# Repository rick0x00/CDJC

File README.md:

# Cascading 4017 Decada/Johnson Counter

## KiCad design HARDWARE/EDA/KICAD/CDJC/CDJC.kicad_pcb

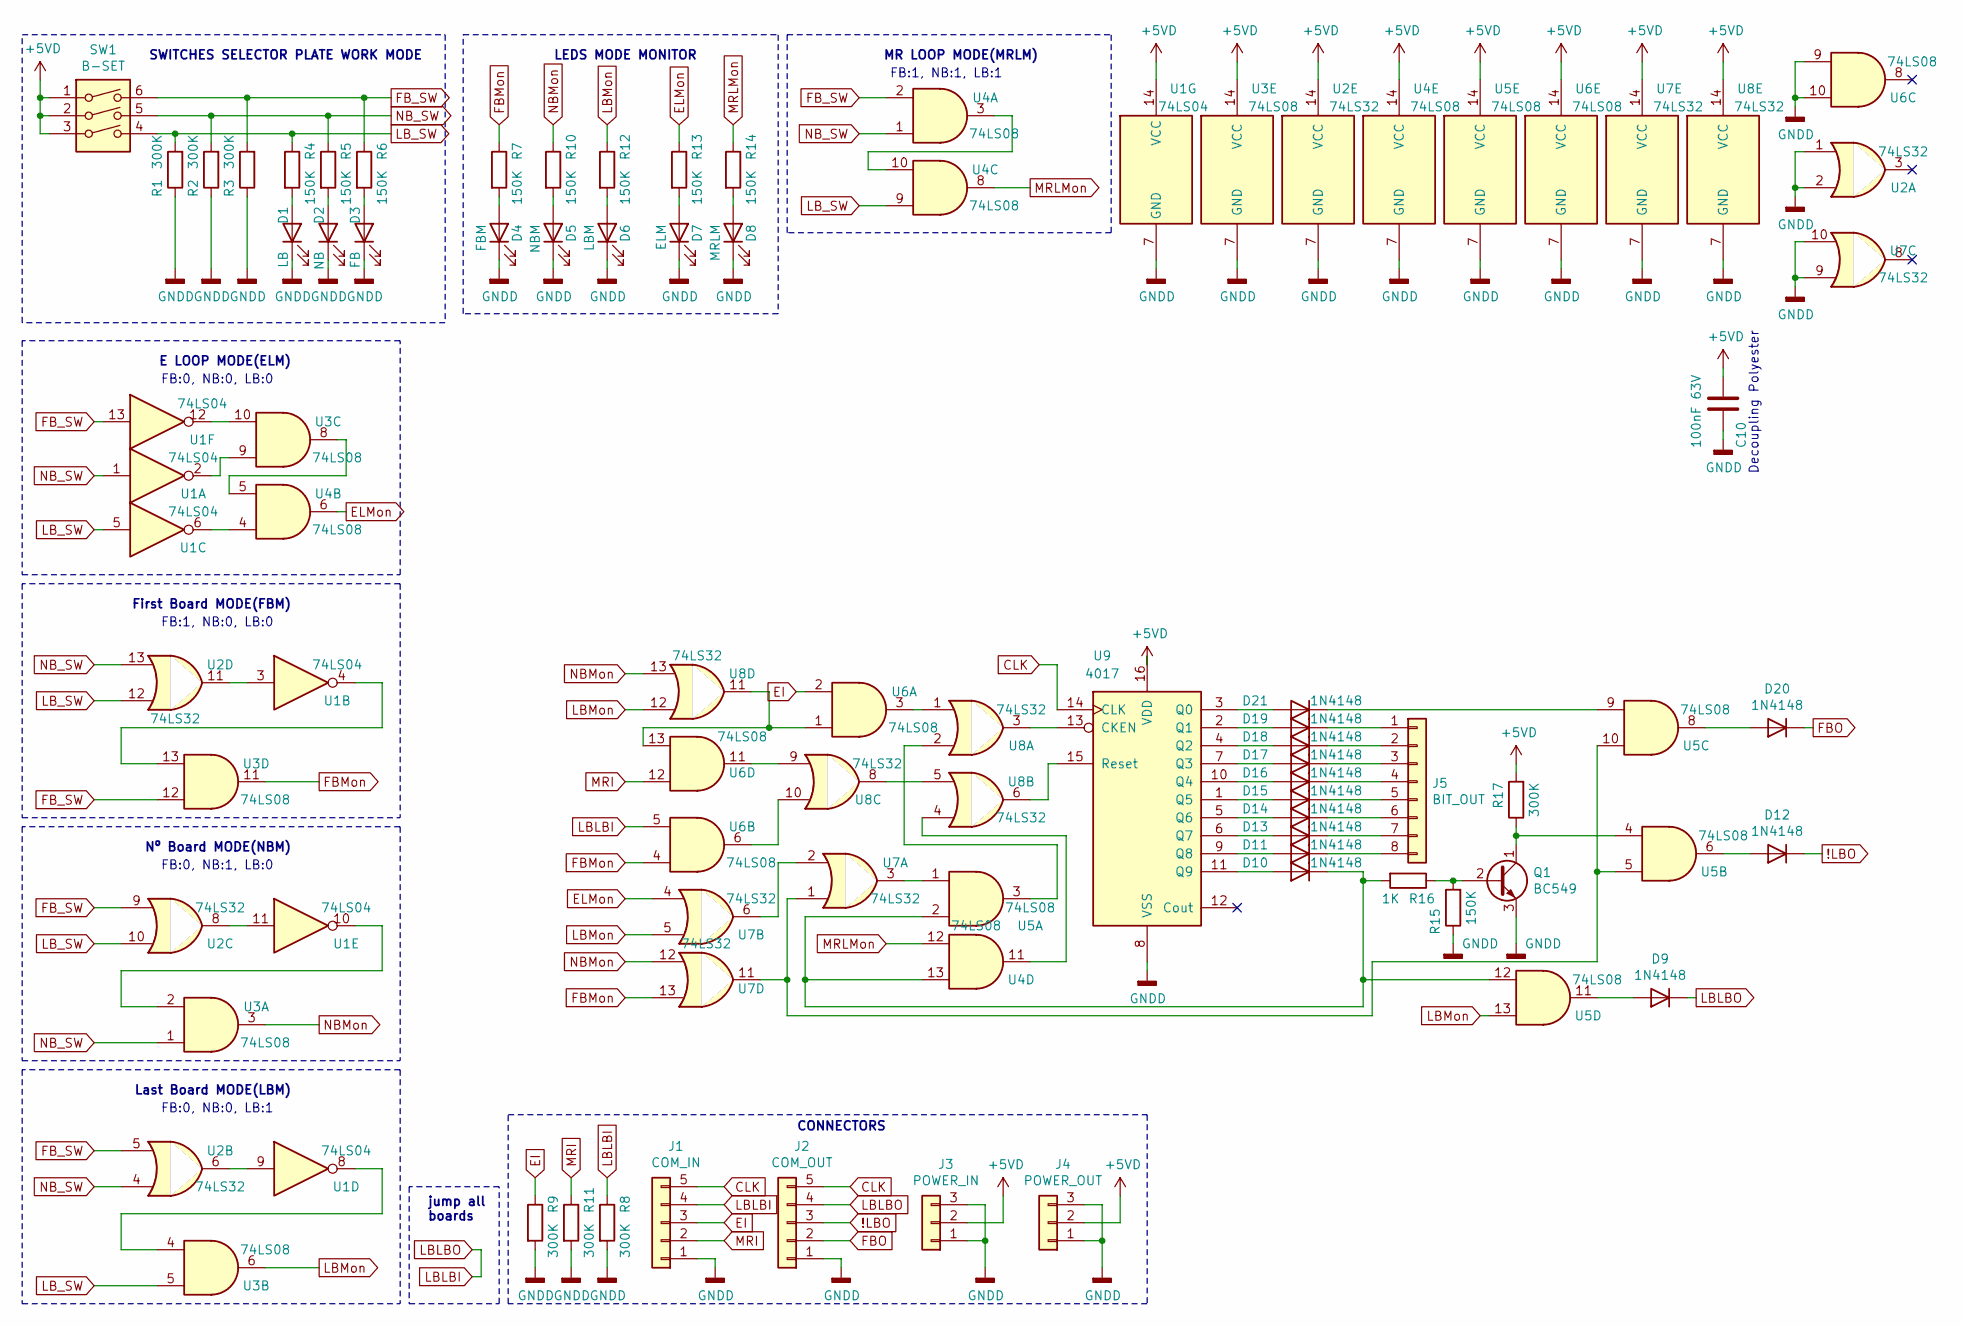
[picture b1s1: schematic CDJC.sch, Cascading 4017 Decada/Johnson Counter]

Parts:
C10: 100nF 63V; C_Rect_L7.0mm_W2.5mm_P5.00mm
D1: LB; LED_D3.0mm
D2: NB; LED_D3.0mm
D3: FB; LED_D3.0mm
D4: FBM; LED_D3.0mm
D5: NBM; LED_D3.0mm
D6: LBM; LED_D3.0mm
D7: ELM; LED_D3.0mm
D8: MRLM; LED_D3.0mm
D9, D10, D11, D12, D13, D14, D15, D16, D17, D18, D19, D20: 1N4148; D_DO-34_SOD68_P7.62mm_Horizontal
D21: 1N4148; D_DO-34_SOD68_P12.70mm_Horizontal
J1: COM_IN; PinHeader_1x05_P2.54mm_Horizontal
J2: COM_OUT; PinSocket_1x05_P2.54mm_Horizontal
J3: POWER_IN; PinHeader_1x03_P2.54mm_Horizontal
J4: POWER_OUT; PinSocket_1x03_P2.54mm_Horizontal
J5: BIT_OUT; PinSocket_1x08_P2.54mm_Horizontal
Q1: BC549; TO-92_Inline
R1, R2, R3, R8, R9, R11, R17: 300K; R_Axial_DIN0207_L6.3mm_D2.5mm_P7.62mm_Horizontal
R4, R5, R6, R7, R10, R12, R13, R14, R15: 150K; R_Axial_DIN0207_L6.3mm_D2.5mm_P7.62mm_Horizontal
R16: 1K; R_Axial_DIN0207_L6.3mm_D2.5mm_P7.62mm_Horizontal
SW1: B-SET; SW_DIP_SPSTx03_Slide_9.78x9.8mm_W7.62mm_P2.54mm
U1: 74LS04; DIP-14_W7.62mm_LongPads
U2, U7, U8: 74LS32; DIP-14_W7.62mm_LongPads
U3, U4, U5, U6: 74LS08; DIP-14_W7.62mm_LongPads
U9: 4017; DIP-16_W7.62mm_LongPads

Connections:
!LBO: D12.1 (K), J2.3
+5VD: C10.1, J3.2, J4.2, R17.2, SW1.1, SW1.2, SW1.3, U1.14 (VCC), U2.14 (VCC), U3.14 (VCC), U4.14 (VCC), U5.14 (VCC), U6.14 (VCC), U7.14 (VCC), U8.14 (VCC), U9.16 (VDD)
CLK: J1.5, J2.5, U9.14 (CLK)
EI: J1.3, R9.1, U6.2
ELMon: R13.1, U4.6, U7.4
FBMon: R7.1, U3.11, U6.4, U7.13
FBO: D20.1 (K), J2.2
FB_SW: R3.2, R6.1, SW1.6, U1.13, U2.5, U2.9, U3.12, U4.2
GNDD: C10.2, D1.1 (K), D2.1 (K), D3.1 (K), D4.1 (K), D5.1 (K), D6.1 (K), D7.1 (K), D8.1 (K), J1.1, J2.1, J3.1, J3.3, J4.1, J4.3, Q1.3 (E), R1.1, R2.1, R3.1, R8.2, R9.2, R11.2, R15.1, U1.7 (GND), U2.1, U2.2, U2.7 (GND), U3.7 (GND), U4.7 (GND), U5.7 (GND), U6.7 (GND), U6.9, U6.10, U7.7 (GND), U7.9, U7.10, U8.7 (GND), U9.8 (VSS)
LBLBI: D9.1 (K), J1.4, J2.4, R8.1, U6.5
LBMon: R12.1, U3.6, U5.13, U7.5, U8.12
LB_SW: R1.2, R4.1, SW1.4, U1.5, U2.10, U2.12, U3.5, U4.9
MRI: J1.2, R11.1, U6.12
MRLMon: R14.1, U4.8, U4.12
NBMon: R10.1, U3.3, U7.12, U8.13
NB_SW: R2.2, R5.1, SW1.5, U1.1, U2.4, U2.13, U3.1, U4.1
unnamed: D1.2 (A), R4.2
unnamed: D2.2 (A), R5.2
unnamed: D3.2 (A), R6.2
unnamed: D4.2 (A), R7.2
unnamed: D5.2 (A), R10.2
unnamed: D6.2 (A), R12.2
unnamed: D7.2 (A), R13.2
unnamed: D8.2 (A), R14.2
unnamed: D9.2 (A), U5.11
unnamed: D10.1 (K), R16.2, U4.13, U5.2, U5.12
unnamed: D10.2 (A), U9.11 (Q9)
unnamed: D11.1 (K), J5.8
unnamed: D11.2 (A), U9.9 (Q8)
unnamed: D12.2 (A), U5.6
unnamed: D13.1 (K), J5.7
unnamed: D13.2 (A), U9.6 (Q7)
unnamed: D14.1 (K), J5.6
unnamed: D14.2 (A), U9.5 (Q6)
unnamed: D15.1 (K), J5.5
unnamed: D15.2 (A), U9.1 (Q5)
unnamed: D16.1 (K), J5.4
unnamed: D16.2 (A), U9.10 (Q4)
unnamed: D17.1 (K), J5.3
unnamed: D17.2 (A), U9.7 (Q3)
unnamed: D18.1 (K), J5.2
unnamed: D18.2 (A), U9.4 (Q2)
unnamed: D19.1 (K), J5.1
unnamed: D19.2 (A), U9.2 (Q1)
unnamed: D20.2 (A), U5.8
unnamed: D21.1 (K), U5.9
unnamed: D21.2 (A), U9.3 (Q0)
unnamed: Q1.1 (C), R17.1, U5.4
unnamed: Q1.2 (B), R15.2, R16.1
unnamed: U1.2, U3.9
unnamed: U1.3, U2.11
unnamed: U1.4, U3.13
unnamed: U1.6, U4.4
unnamed: U1.8, U3.4
unnamed: U1.9, U2.6
unnamed: U1.10, U3.2
unnamed: U1.11, U2.8
unnamed: U1.12, U3.10
unnamed: U3.8, U4.5
unnamed: U4.3, U4.10
unnamed: U4.11, U8.4
unnamed: U5.1, U7.3
unnamed: U5.3, U8.2
unnamed: U5.5, U5.10, U7.1, U7.11
unnamed: U6.1, U6.13, U8.11
unnamed: U6.3, U8.1
unnamed: U6.6, U8.10
unnamed: U6.11, U8.9
unnamed: U7.2, U7.6
unnamed: U8.3, U9.13 (CKEN)
unnamed: U8.5, U8.8
unnamed: U8.6, U9.15 (Reset)

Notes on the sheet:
SWITCHES SELECTOR PLATE WORK MODE
MR LOOP MODE(MRLM)
FB:1, NB:1, LB:1
E LOOP MODE(ELM)
FB:0, NB:0, LB:0
First Board MODE(FBM)
FB:1, NB:0, LB:0
Nº Board MODE(NBM)
FB:0, NB:1, LB:0
Last Board MODE(LBM)
FB:0, NB:0, LB:1
LEDS MODE MONITOR
Decoupling Polyester
CONNECTORS
jump all boards

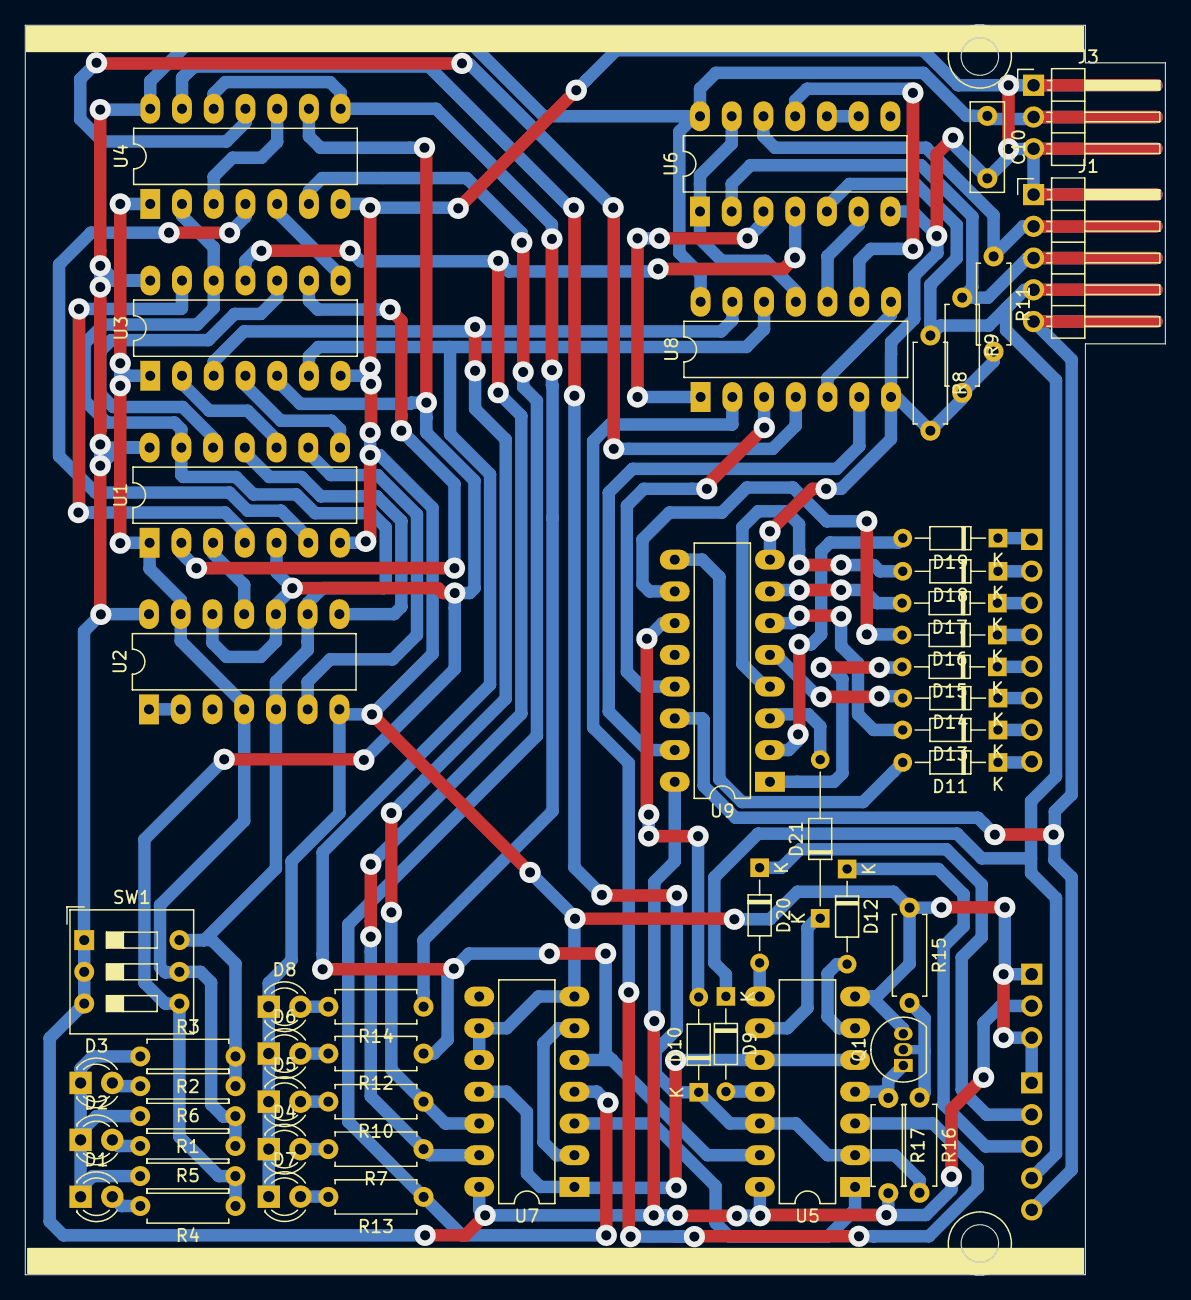
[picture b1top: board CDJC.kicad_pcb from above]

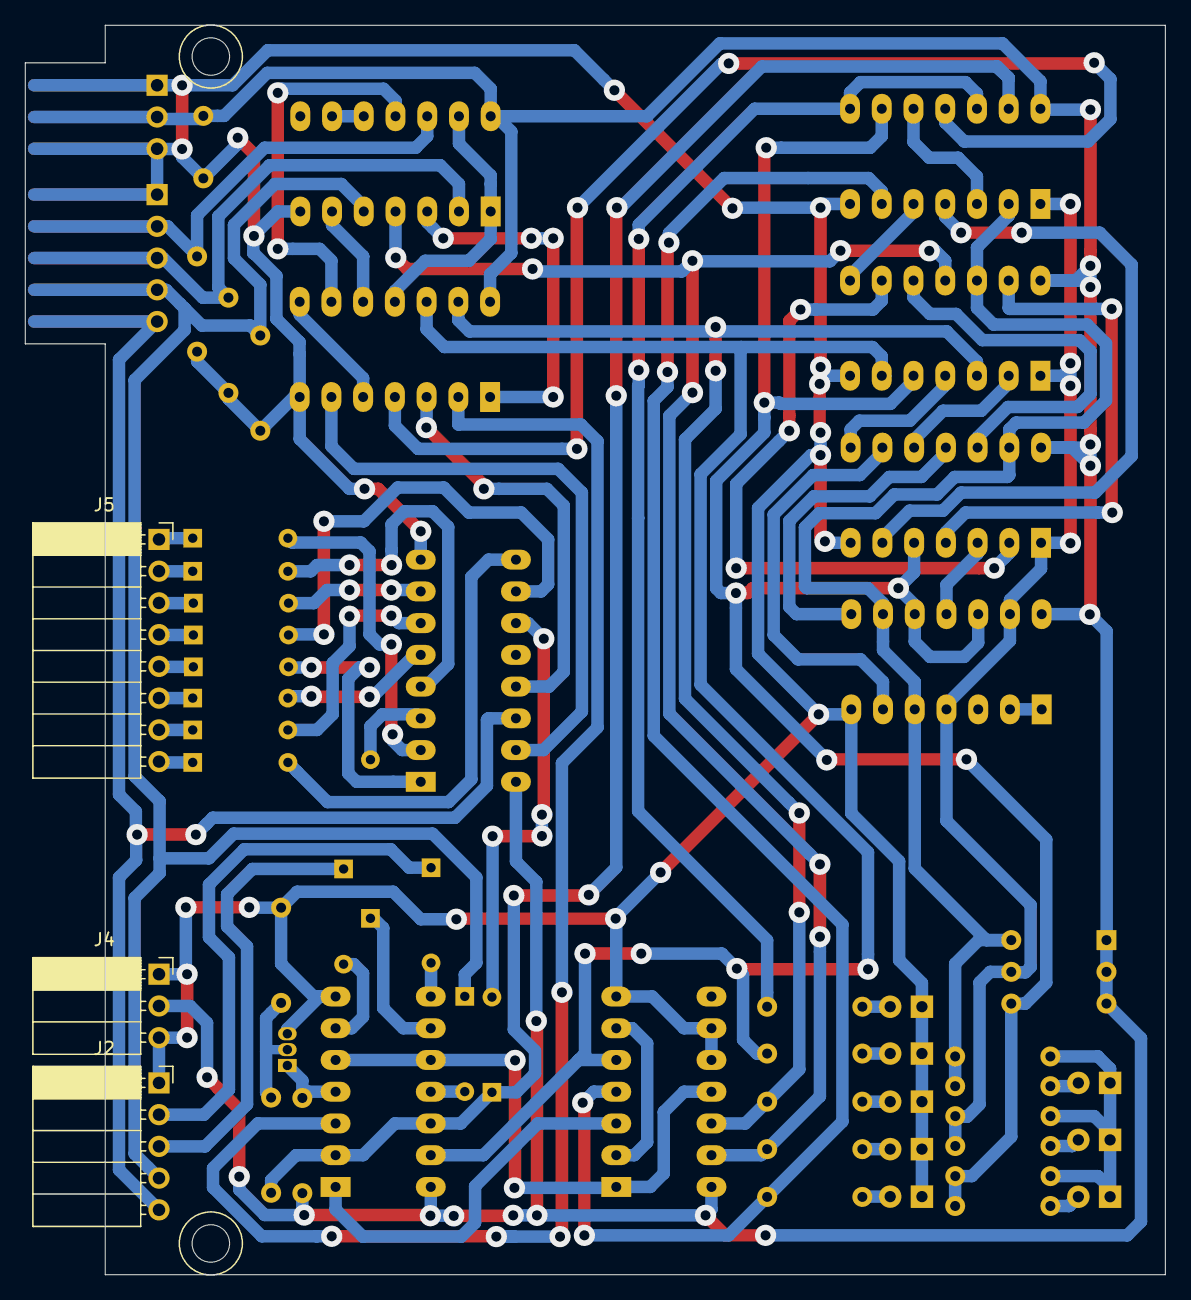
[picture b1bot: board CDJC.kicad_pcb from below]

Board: 2 copper layers, 91.2 x 100.0 mm, 55 parts (3 on the bottom side), 72 nets.

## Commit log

2021-09-26 add kicad project
2021-09-26 kicad project start
2021-09-26 CONTROL SWITCHS OK
2021-09-26 CONNECTORS OK
2021-09-26 capacitor decoupling OK
2021-09-26 OUTPUTS 4017 PK
2021-09-26 CONNECTORS REMIX
2021-09-26 finished project
2021-09-27 paused PCB design
2021-09-27 i am crazy
2021-09-27 PCI connector OK
2021-09-27 stop work
2021-09-28 work stop
2021-09-28 adjust layout pcb
2021-09-29 Adjust resitor alingment
2021-09-29 ajust dip and leds mode set
    adjust jumper to set mode
2021-09-29 adjust footprint to bc 547
2021-09-29 stop work, go home
2021-09-30 pause work for sleep
2021-09-30 adjusting PCB
2021-10-01 sleep
2021-10-02 pause work
2021-10-03 pause work0
2021-10-04 ajdust PCB
2021-10-05 remaining editions
2021-10-05 adjusts in PCB
2021-10-05 Re-associate footprints by reference
2021-10-07 U7 pre adjust in PCB
2021-10-07 finished V1 board
2021-10-07 ADD IMAGE IN README
2021-10-07 tentativa de conversão 3D
2021-10-08 PCB finished
